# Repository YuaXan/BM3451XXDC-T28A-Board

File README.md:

<div align="center">
<h1>
<a href="https://github.com/YuaXan/BM3451XXDC-T28A-Board">BM3451XXDC-T28A-Board</a></h1>

**Rechargeable battery protection board based on BM3451 IC**
______________________________________________________________________

</div>

## Product Introduction
The board uses `BM3451XXDC-T28A` to protect 3/4/5 cells rechargeable battery pack. the IC works constantly to monitor each cell’s voltage, the current of charge or discharge, and the temperature of the environment to provide overcharge, over-discharge, discharge overcurrent, short circuit, charge overcurrent, and over-temperature protections, etc. Besides, it also can change the protection delay time of overcharge, over-discharge, and discharge overcurrent by setting the external capacitors.

## Application Scenarios
1. Power tools
2. Electric bicycle
3. UPS applications
4. etc.

## Product Description
The board's power supply voltage range is 5-30V, charge or discharge current MAX is 30A. 

The four MOSFET `Q8`, `Q9`, `Q10`, `Q11` and tow jepsun current resistor `RSENSE1` and `RSENSE2` can be replaced to achieve higher current output. 

---

Select the number of cells based on whether `RSET1` and `RSET2` are mounted with 0Ω resistors.

When `RSET1` and `RSET2` all not mounting with 0Ω resistors leads to the `SET` pin in a floating state, and the board can connect 5 cells. 
When `RSET1` is mounting with resistors, `RSET2` is not mounting with resistors, and short circuits `B1` and `B-`, the board can connect 4 cells.
When `RSET1` is not mounting with resistors, and `RSET2` is mounting with resistors, and short circuits `B2`, `B1`, and `B-`, the board can connect 3 cells.

**[Warning]: Not `RSET1` and `RSET2` all to mounting with 0Ω resistors, this behavior will cause a short circuit**

---

There are five LEDs to monitor the balancing status of the cells. When one of the LEDs is lit, it means that the corresponding cell is starting to balance. 
 
`LED1`, `LED2`, `LED3`, `LED4`, and `LED5` correspond to `B1`, `B2`, `B3`, `B4`, and `B5` respectively:

 ---
 
At the same time, the `DO` and `CO` pins correspond to `DO_LED1` and `CO_LED1` respectively. This allows you to check the discharge and charge status. 

 ---
 
Safe and reliable by providing control discharge overcurrent release terminals with optical coupler.

Control of `OCCT` pin is via `XH P2.5mm 3pin` terminal.

**[Warning]: The `OCCT` pin has not been tested. Usage instructions are not provided in the datasheet. Usage instructions will be provided after board testing.**

## Instruction Manual
The board connection diagram is shown in the image.

## TODO
- [ ] The board is manufactured.
- [ ] The board is testing.
- [ ] Know how `OCCT` works.
- [ ] The donation channel is open.

## Contributions
Every contribution to this repository is highly appreciated! If you spot any bug or problem, open a issue or pull request so that it can be rectified for everyone.

For feature requests: Please open a issue and I'll add the feature in a future release once I get some time in my hands.

## Donors
The donation channel is not currently open, so stay tuned.

## License
For e-enthusiasts or geeks, follow the [CC-BY-NC-SA 4.0](/LICENSE.txt) license. For contributors and donors you can follow the [CC-BY 4.0](/LICENSE-CC-BY-4.0.txt) license, which means that commercial use is supported and distributed freely.

## Information
[BM3451XXDC-T28A DataSheet](http://www.bydmicro.com/params/field/preview/PDF_PRODUCT_202304141002.pdf)

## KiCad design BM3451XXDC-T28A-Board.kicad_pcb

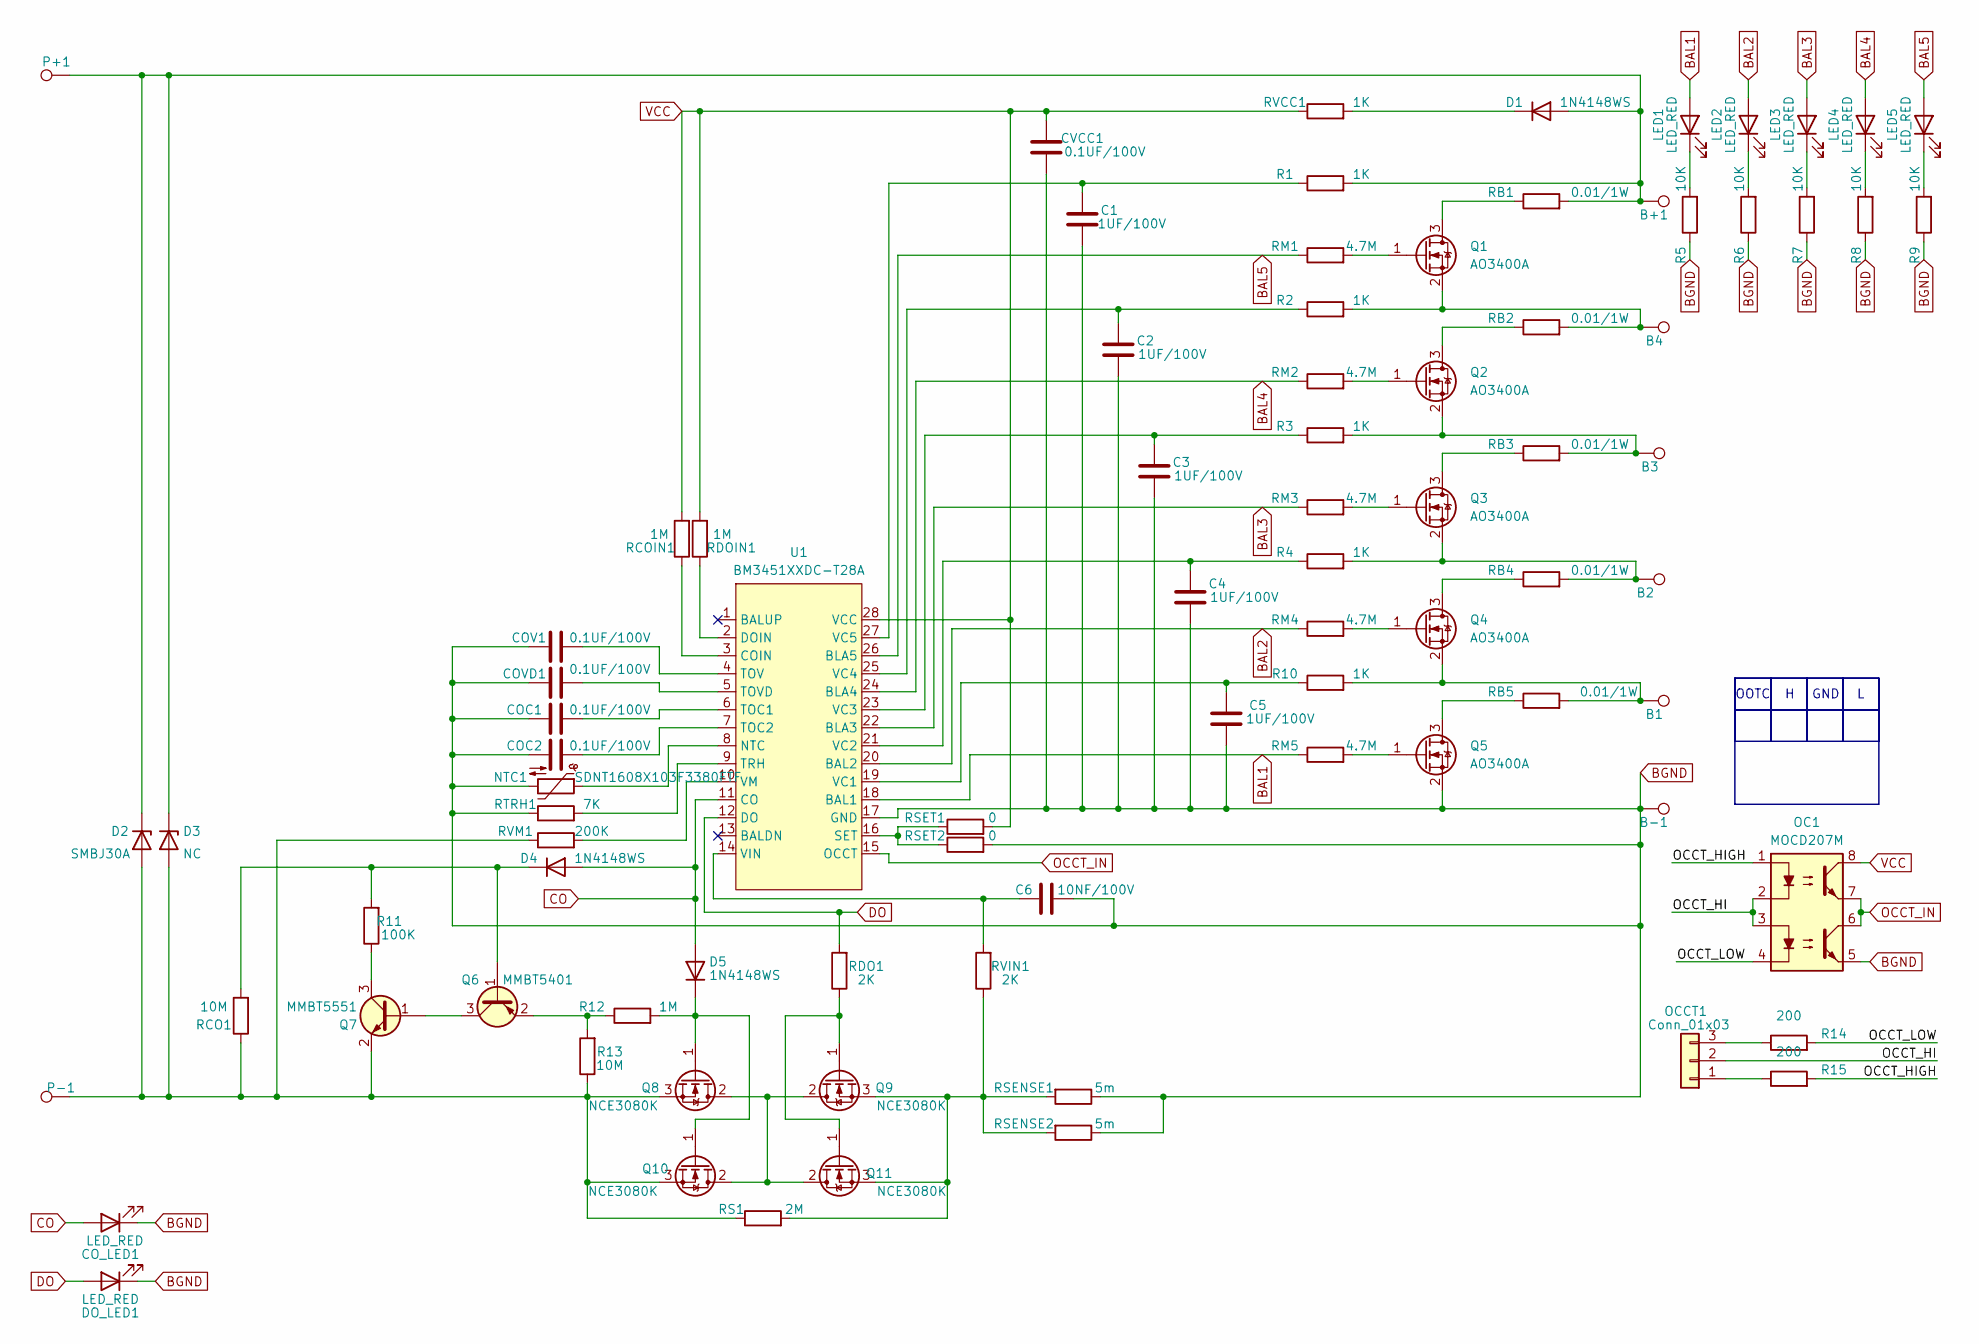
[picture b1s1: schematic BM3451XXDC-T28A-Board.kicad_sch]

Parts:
B1, B2, B3, B4: TestPoint; TestPoint_Pad_4.0x4.0mm
B+1: TestPoint; TestPoint_Pad_4.0x4.0mm
B-1: TestPoint; TestPoint_Pad_4.0x4.0mm
C1, C2, C3, C4, C5: 1UF/100V; C_0603_1608Metric
C6: 10NF/100V; C_0603_1608Metric
COC1, COC2: 0.1UF/100V; C_0603_1608Metric
COV1: 0.1UF/100V; C_0603_1608Metric
COVD1: 0.1UF/100V; C_0603_1608Metric
CO_LED1: LED_RED; LED_0603_1608Metric
CVCC1: 0.1UF/100V; C_0603_1608Metric
D1, D4, D5: 1N4148WS; D_SOD-323
D2: SMBJ30A; D_SMB
D3: NC; D_SMB
DO_LED1: LED_RED; LED_0603_1608Metric
LED1, LED2, LED3, LED4, LED5: LED_RED; LED_0603_1608Metric
NTC1: SDNT1608X103F3380FTF; R_0603_1608Metric
OC1: MOCD207M; SO-8_3.9x4.9mm_P1.27mm
OCCT1: Conn_01x03; JST_XH_B3B-XH-A_1x03_P2.50mm_Vertical
P+1: TestPoint; TestPoint_Pad_4.0x4.0mm
P-1: TestPoint; TestPoint_Pad_4.0x4.0mm
Q1, Q2, Q3, Q4, Q5: AO3400A; SOT-23
Q6: MMBT5401; SOT-23
Q7: MMBT5551; SOT-23
Q8, Q9, Q10, Q11: NCE3080K; TO-252-2
R1, R2, R3, R4, R10: 1K; R_0603_1608Metric
R5, R6, R7, R8, R9: 10K; R_0603_1608Metric
R11: 100K; R_0603_1608Metric
R12: 1M; R_0603_1608Metric
R13: 10M; R_0603_1608Metric
R14, R15: 200; R_0603_1608Metric
RB1, RB2, RB3, RB4, RB5: 0.01/1W; R_1206_3216Metric
RCO1: 10M; R_0603_1608Metric
RCOIN1: 1M; R_0603_1608Metric
RDO1: 2K; R_0603_1608Metric
RDOIN1: 1M; R_0603_1608Metric
RM1, RM2, RM3, RM4, RM5: 4.7M; R_0603_1608Metric
RS1: 2M; R_0603_1608Metric
RSENSE1, RSENSE2: 5m; R_2512_6332Metric
RSET1, RSET2: 0; R_0603_1608Metric
RTRH1: 7K; R_0603_1608Metric
RVCC1: 1K; R_0603_1608Metric
RVIN1: 2K; R_0603_1608Metric
RVM1: 200K; R_0603_1608Metric
U1: BM3451XXDC-T28A; TSSOP-28_4.4x9.7mm_P0.65mm

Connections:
/OCCT_HI: OC1.2, OC1.3, OCCT1.2; also elsewhere on the board
/OCCT_HIGH: OC1.1, R15.2
/OCCT_LOW: OC1.4, R14.2
BAL1: LED1.2 (A), RM5.1, U1.18 (BAL1)
BAL2: LED2.2 (A), RM4.1, U1.20 (BAL2)
BAL3: LED3.2 (A), RM3.1, U1.22 (BLA3)
BAL4: LED4.2 (A), RM2.1, U1.24 (BLA4)
BAL5: LED5.2 (A), RM1.1, U1.26 (BLA5)
BGND: B-1.1, C1.1, C2.1, C3.1, C4.1, C5.1, C6.1, COC1.1, COC2.1, COV1.1, COVD1.1, CO_LED1.1 (K), CVCC1.1, DO_LED1.1 (K), NTC1.2, OC1.5, Q5.2 (S), R5.1, R6.1, R7.1, R8.1, R9.1, RSENSE1.1, RSENSE2.1, RSET2.2, RTRH1.1, U1.17 (GND); also elsewhere on the board
CO: CO_LED1.2 (A), D4.2 (A), D5.2 (A), U1.11 (CO)
DO: DO_LED1.2 (A), RDO1.2, U1.12 (DO)
unnamed 11: B+1.1, D1.2 (A), D2.1 (K), D3.1 (K), P+1.1, R1.2, RB1.2; also elsewhere on the board
unnamed: D1.1 (K), RVCC1.2
unnamed 13: D2.2 (A), D3.2 (A), P-1.1, Q7.2 (E), Q8.3 (S), Q10.3 (S), R13.1, RCO1.1, RS1.1, RVM1.1; also elsewhere on the board
unnamed: D4.1 (K), Q6.1 (B), R11.2, RCO1.2
unnamed: D5.1 (K), Q8.1 (G), Q10.1 (G), R12.2
unnamed: LED1.1 (K), R5.2
unnamed: LED2.1 (K), R6.2
unnamed: LED3.1 (K), R7.2
unnamed: LED4.1 (K), R8.2
unnamed: LED5.1 (K), R9.2
unnamed 21: OCCT1.1, R15.1; also elsewhere on the board
unnamed 22: OCCT1.3, R14.1; also elsewhere on the board
unnamed: Q1.3 (D), RB1.1
unnamed: Q1.1 (G), RM1.2
unnamed: B4.1, Q1.2 (S), R2.2, RB2.2
unnamed: Q2.3 (D), RB2.1
unnamed: Q2.1 (G), RM2.2
unnamed: B3.1, Q2.2 (S), R3.2, RB3.2
unnamed: Q3.3 (D), RB3.1
unnamed: Q3.1 (G), RM3.2
unnamed: B2.1, Q3.2 (S), R4.2, RB4.2
unnamed: Q4.3 (D), RB4.1
unnamed: Q4.1 (G), RM4.2
unnamed: B1.1, Q4.2 (S), R10.2, RB5.2
unnamed: Q5.3 (D), RB5.1
unnamed: Q5.1 (G), RM5.2
unnamed: Q6.3 (C), Q7.1 (B)
unnamed: Q6.2 (E), R12.1, R13.2
unnamed: Q7.3 (C), R11.1
unnamed: Q8.2 (D), Q9.2 (D), Q10.2 (D), Q11.2 (D)
unnamed: Q9.1 (G), Q11.1 (G), RDO1.1
unnamed: Q9.3 (S), Q11.3 (S), RS1.2, RSENSE1.2, RSENSE2.2, RVIN1.1
unnamed: RCOIN1.1, U1.3 (COIN)
unnamed: RDOIN1.1, U1.2 (DOIN)
unnamed: NTC1.1, U1.8 (NTC)
unnamed: RSET1.1, RSET2.1, U1.16 (SET)
unnamed: COC1.2, U1.6 (TOC1)
unnamed: COC2.2, U1.7 (TOC2)
unnamed: COV1.2, U1.4 (TOV)
unnamed: COVD1.2, U1.5 (TOVD)
unnamed: RTRH1.2, U1.9 (TRH)
unnamed: C5.2, R10.1, U1.19 (VC1)
unnamed: C4.2, R4.1, U1.21 (VC2)
unnamed: C3.2, R3.1, U1.23 (VC3)
unnamed: C2.2, R2.1, U1.25 (VC4)
unnamed: C1.2, R1.1, U1.27 (VC5)
unnamed: C6.2, RVIN1.2, U1.14 (VIN)
unnamed: RVM1.2, U1.10 (VM)
OCCT_IN: OC1.6, OC1.7, U1.15 (OCCT)
VCC: CVCC1.2, OC1.8, RCOIN1.2, RDOIN1.2, RSET1.2, RVCC1.1, U1.28 (VCC)

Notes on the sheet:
GND
OOTC

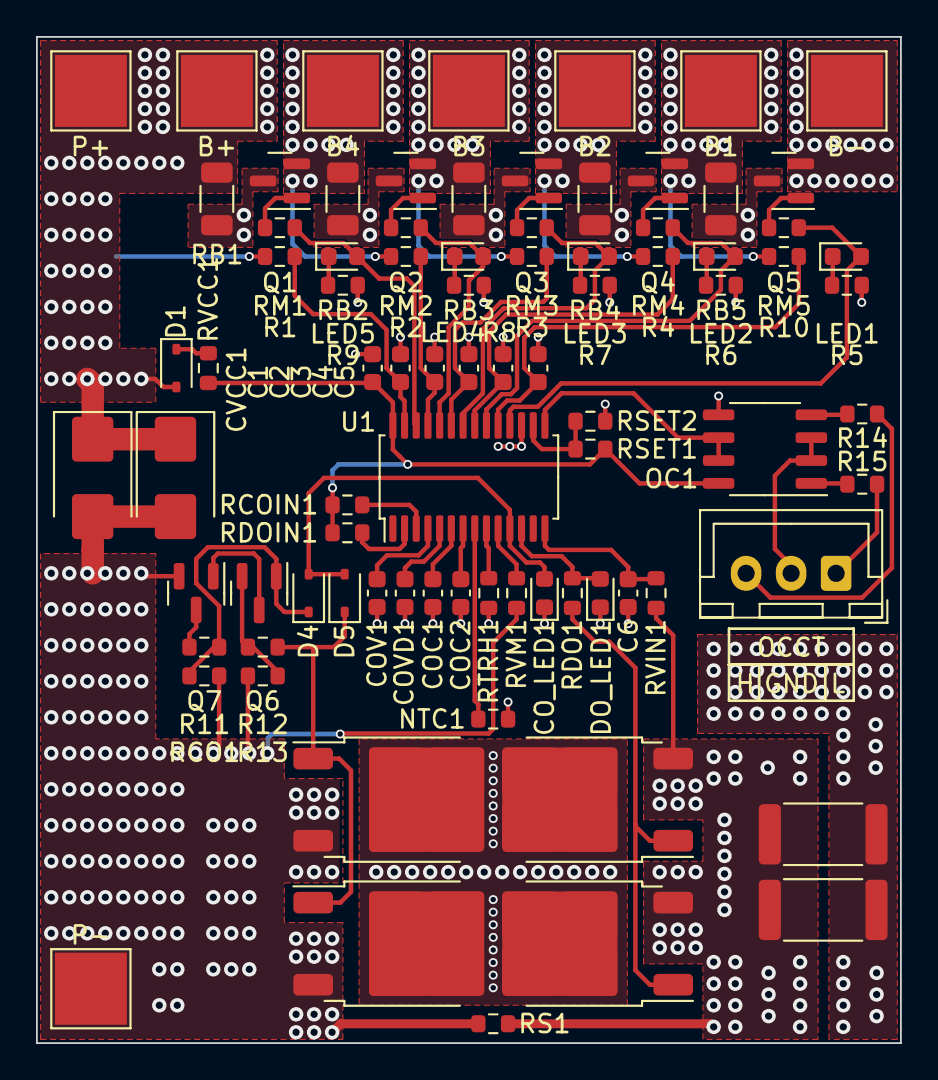
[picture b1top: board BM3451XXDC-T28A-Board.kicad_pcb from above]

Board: 2 copper layers, 48.0 x 55.9 mm, 84 parts (0 on the bottom side), 61 nets.

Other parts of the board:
B+: TestPoint; TestPoint_Pad_4.0x4.0mm
B-: TestPoint; TestPoint_Pad_4.0x4.0mm
OCCT: Conn_01x03; JST_XH_B3B-XH-A_1x03_P2.50mm_Vertical
P+: TestPoint; TestPoint_Pad_4.0x4.0mm
P-: TestPoint; TestPoint_Pad_4.0x4.0mm

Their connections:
/OCCT_HI: OCCT.2; also elsewhere on the board
BGND: B-.1; also elsewhere on the board
unnamed 11: B+.1, P+.1; also elsewhere on the board
unnamed 13: P-.1; also elsewhere on the board
unnamed 21: OCCT.1; also elsewhere on the board
unnamed 22: OCCT.3; also elsewhere on the board

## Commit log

2024-02-03 Change to a CC BY-NC-SA 4.0 License and add .gitignore
2024-02-04 Submit readme.md and some images
2024-02-04 fix readme.md
2024-02-04 add CODE_OF_CONDUCT.md
2024-02-04 update README and CHANGELOG

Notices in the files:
README.md:
License: CC BY-NC-SA 4.0
